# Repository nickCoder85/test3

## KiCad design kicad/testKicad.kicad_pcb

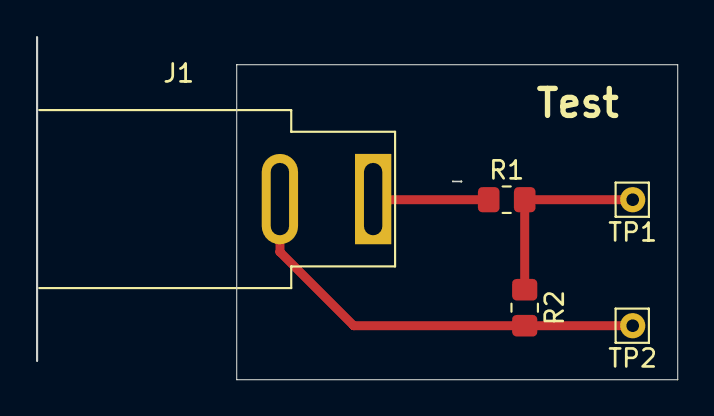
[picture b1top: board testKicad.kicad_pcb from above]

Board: 2 copper layers, 35.6 x 19.0 mm, 5 parts (0 on the bottom side), 3 nets.

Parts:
J1: Jack-DC; BarrelJack_SwitchcraftConxall_RAPC10U_Horizontal
R1, R2: R; R_0805_2012Metric_Pad1.20x1.40mm_HandSolder
TP1: PWR; Pin_D0.7mm_L6.5mm_W1.8mm_FlatFork
TP2: GND; Pin_D0.7mm_L6.5mm_W1.8mm_FlatFork

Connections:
GND: J1.2, R2.2, TP2.1
unnamed: J1.1, R1.1
unnamed: R1.2, R2.1, TP1.1

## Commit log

2025-02-05 new test
2025-02-05 kicad test
2025-02-15 voltage divider circuit
2025-02-16 PCB design
